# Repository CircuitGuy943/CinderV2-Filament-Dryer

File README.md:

# Cinder Filament Dryer - A fully featured 90W filament dryer for all your drying needs!

The cinder filament dryer is a self managed ecosystem comprising of 2 45W heaters powered from a 90W+ power supply to provide the most heating power possible. In addition to that, there is also space for 3 possible fans with silica gel pouch to aid in the airflow and dryer performance. Equiped with an SHT40 module, you will always be 110% aware of exactly how long your filament will take to dry and at what temperature and with a 90W heater, I can guarantee that won't be long ;). Also comes in a cool, tilted design with a fancy flame aesthetic on the side, it also utilizes a smart locking system that adapts the arm of the spool holder to the width of the spool hole, this way, you can ensure the spool is free to spin properly and doesn't scratch the heating element. And if that isn't enough filament flow for you, there is also a dedicated servo driving system and filament extrusion rate feedback integration that automatically pushes out the strand of filament so that the printer, or you, don't have to worry about printing while drying. Comes with a 128x64 OLED, 3 buttons and an encoder for all your "control panel" needs because, we all love fancy control panels don't we? The frame itself is designed to be easy to print (albeit quite large) and assemble. And not to mention with the amazing aesthetic comes a super cool futuristic, pod like door system that lifts upwars on a big pin hinge to allow you to remove the spools or insert more. And obviously, we don't want tipping dryers so, on another pin hinge, we have a leg that can be bent backwards flush to the device when the dryer is hung on the wall or extended so that it literally doesn't fall over.

Some CAD images:

## Features:
- It drys filament (duh)
- 90W heating power
- OLED display control panel with 3 buttons, encoder and a cool acrylic view panel
- Leg (pretty simple) to hold it from falling backwards
- Fully integrated PCB that drives the 90W heaters, stepper motor driver, OLED, buttons and connectors for all the other sensors.
- Filament pushing system with extruding feedback to maintain proper filament pushing flow
- Easy to assemble
- Airflow powered by 3 5020 fans (LOTS of airflow)
- Spaces for silica gel pouches
- Fancy, cool looking tilted design with flame aesthetics
- Automatic locking system for holding the spool with an arm extendible in diameter <sup>TM</sup>
- PWM control of fans and heater

## PCB
And this is my main PCB. A bit budget restrained otherwise so I had to use some premade sensor modules, the actual flex heater PCB is pretty simple so I won't bother putting it here (but it's in the files):

And the Schematic:

And here are some 3D views as well:

## Firmware Overview
At the current moment there is some, untested firmware in there that's supposed to have the dryer functioning but, I don't actually have it yet so I can't test, in future I will program it properly.

## BOM:

- The actual print (alot, probably like 1-2kg+)
- The main PCB (check KiCad files for all the components and external modules)
- 3 5020 fans
- A stepper motor
- Some lasercut acrylic
- MX keycaps (3)
- Some M2 heated inserts and bolts to hold the whole thing togethor

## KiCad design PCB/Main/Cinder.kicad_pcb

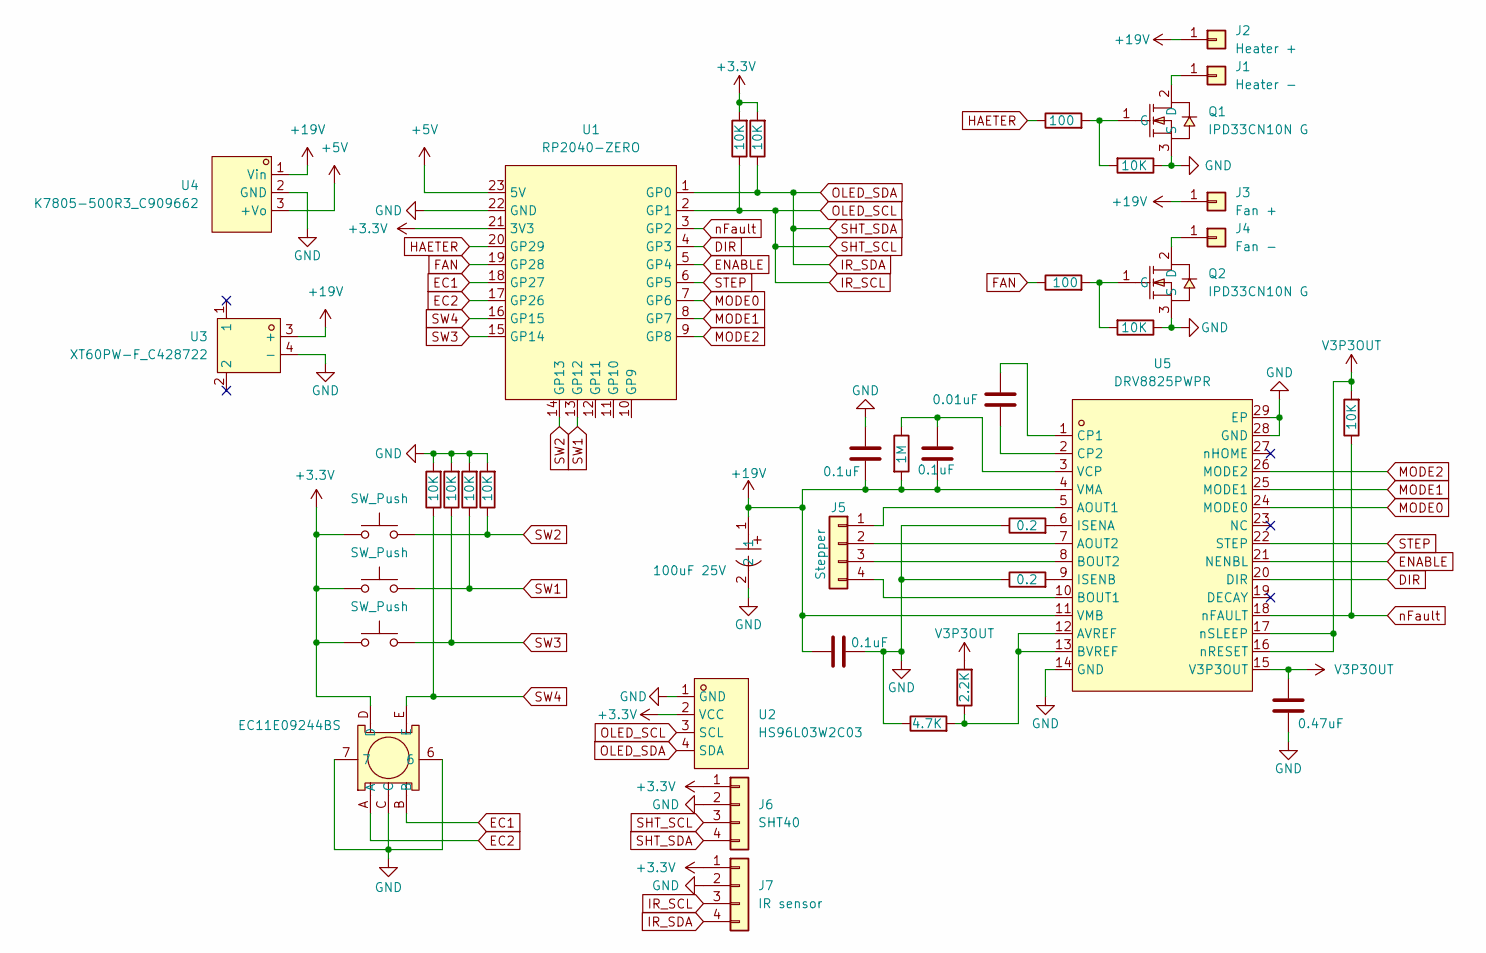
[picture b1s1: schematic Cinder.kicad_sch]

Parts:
C1: 0.01uF; C_1206_3216Metric_Pad1.33x1.80mm_HandSolder
C2, C3, C4: 0.1uF; C_1206_3216Metric_Pad1.33x1.80mm_HandSolder
C5: 0.47uF; C_1206_3216Metric_Pad1.33x1.80mm_HandSolder
J1: Heater -; PinHeader_1x01_P2.54mm_Vertical
J2: Heater +; PinHeader_1x01_P2.54mm_Vertical
J3: Fan +; PinHeader_1x01_P2.54mm_Vertical
J4: Fan -; PinHeader_1x01_P2.54mm_Vertical
J5: Stepper; PinHeader_1x04_P2.54mm_Vertical
J6: SHT40; PinHeader_1x04_P2.54mm_Vertical
J7: IR sensor; PinHeader_1x04_P2.54mm_Vertical
Q1, Q2: IPD33CN10N G; TO-252-2_L6.6-W6.1-P4.57-LS9.9-TL-CW; LCSC Part C536760
R1, R2: 100; R_1206_3216Metric_Pad1.30x1.75mm_HandSolder
R3, R4, R5, R6, R7, R8, R15, R16, R17: 10K; R_1206_3216Metric_Pad1.30x1.75mm_HandSolder
R9: 1M; R_1206_3216Metric_Pad1.30x1.75mm_HandSolder
R10, R11: 0.2; R_1206_3216Metric_Pad1.30x1.75mm_HandSolder
R12: 2.2K; R_1206_3216Metric_Pad1.30x1.75mm_HandSolder
R13: 4.7K; R_1206_3216Metric_Pad1.30x1.75mm_HandSolder
SW1, SW2, SW3: SW_Push; SW_Cherry_MX_1.00u_PCB
SW9: EC11E09244BS; SW-TH_EC11XXXXXXXX; LCSC Part C470742
U1: RP2040-ZERO; COMM-SMD_RP2040-ZERO; LCSC Part C5350143
U2: HS96L03W2C03; OLED-TH_L27.8-W27.2-P2.54_C9900033791; LCSC Part C5248080
U3: XT60PW-F_C428722; TH_2P-XT60PW-F; LCSC Part C428722
U4: K7805-500R3_C909662; PWRM-TH_K78XX-500R3; LCSC Part C909662
U5: DRV8825PWPR; HTSSOP-28_L9.7-W4.4-P0.65-LS6.4-BL-EP5.5; LCSC Part C81582
U6: 100uF 25V; CAP-SMD_BD6.3-L6.6-W6.6-LS7.2-FD-1; LCSC Part C970685

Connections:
+3.3V: J6.1, J7.1, R16.2, R17.2, SW1.1, SW2.1, SW3.1, SW9.D, U1.21 (3V3), U2.2 (VCC)
+5V: U1.23 (5V), U4.3 (+Vo)
+19V: C2.2, C3.1, C4.1, J2.1, J3.1, R9.2, U3.3 (+), U4.1 (Vin), U5.4 (VMA), U5.11 (VMB), U6.1
DIR: U1.4 (GP3), U5.20 (DIR)
EC1: SW9.B, U1.18 (GP27)
EC2: SW9.A, U1.17 (GP26)
ENABLE: U1.5 (GP4), U5.21 (NENBL)
FAN: R2.1, U1.19 (GP28)
GND: C3.2, C4.2, C5.2, J6.2, J7.2, Q1.3 (S), Q2.3 (S), R3.1, R4.1, R5.2, R6.2, R7.2, R8.2, R10.1, R11.1, R13.1, SW9.6, SW9.7, SW9.C, U1.22 (GND), U2.1 (GND), U3.4 (-), U4.2 (GND), U5.14 (GND), U5.28 (GND), U5.29 (EP), U6.2
HAETER: R1.1, U1.20 (GP29)
IR_SCL: J6.3, J7.3, R16.1, U1.2 (GP1), U2.3 (SCL)
IR_SDA: J6.4, J7.4, R17.1, U1.1 (GP0), U2.4 (SDA)
MODE0: U1.7 (GP6), U5.24 (MODE0)
MODE1: U1.8 (GP7), U5.25 (MODE1)
MODE2: U1.9 (GP8), U5.26 (MODE2)
unnamed: J1.1, Q1.2 (D)
unnamed: J4.1, Q2.2 (D)
unnamed: J5.1, U5.5 (AOUT1)
unnamed: J5.2, U5.7 (AOUT2)
unnamed: J5.3, U5.8 (BOUT2)
unnamed: J5.4, U5.10 (BOUT1)
unnamed: Q1.1 (G), R1.2, R4.2
unnamed: Q2.1 (G), R2.2, R3.2
unnamed: R12.1, R13.2, U5.12 (AVREF), U5.13 (BVREF)
unnamed: C1.1, U5.1 (CP1)
unnamed: C1.2, U5.2 (CP2)
unnamed: R10.2, U5.6 (ISENA)
unnamed: R11.2, U5.9 (ISENB)
unnamed: C2.1, R9.1, U5.3 (VCP)
STEP: U1.6 (GP5), U5.22 (STEP)
SW1: R6.1, SW1.2, U1.13 (GP12)
SW2: R5.1, SW2.2, U1.14 (GP13)
SW3: R7.1, SW3.2, U1.15 (GP14)
SW4: R8.1, SW9.E, U1.16 (GP15)
V3P3OUT: C5.1, R12.2, R15.2, U5.15 (V3P3OUT), U5.16 (nRESET), U5.17 (nSLEEP)
nFault: R15.1, U1.3 (GP2), U5.18 (nFAULT)

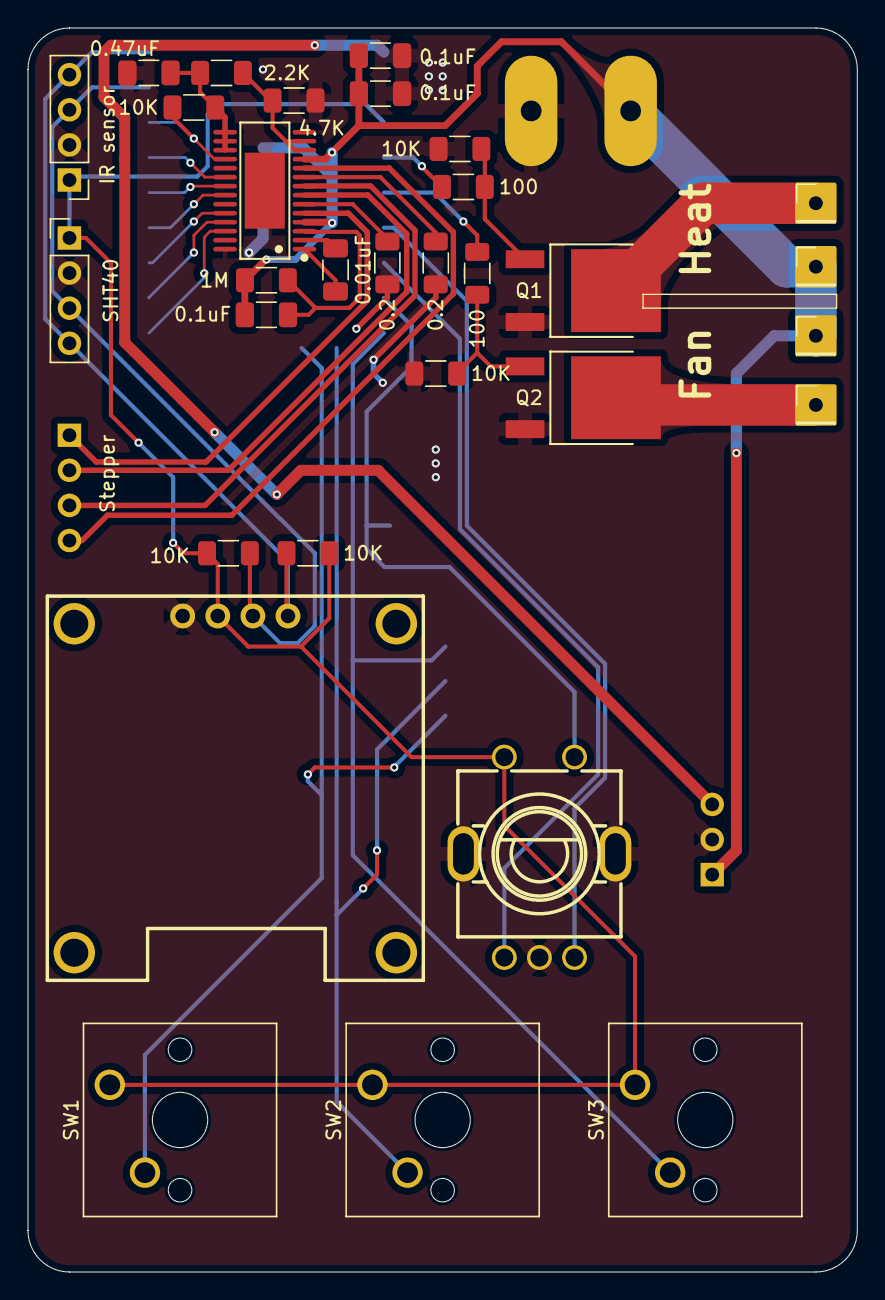
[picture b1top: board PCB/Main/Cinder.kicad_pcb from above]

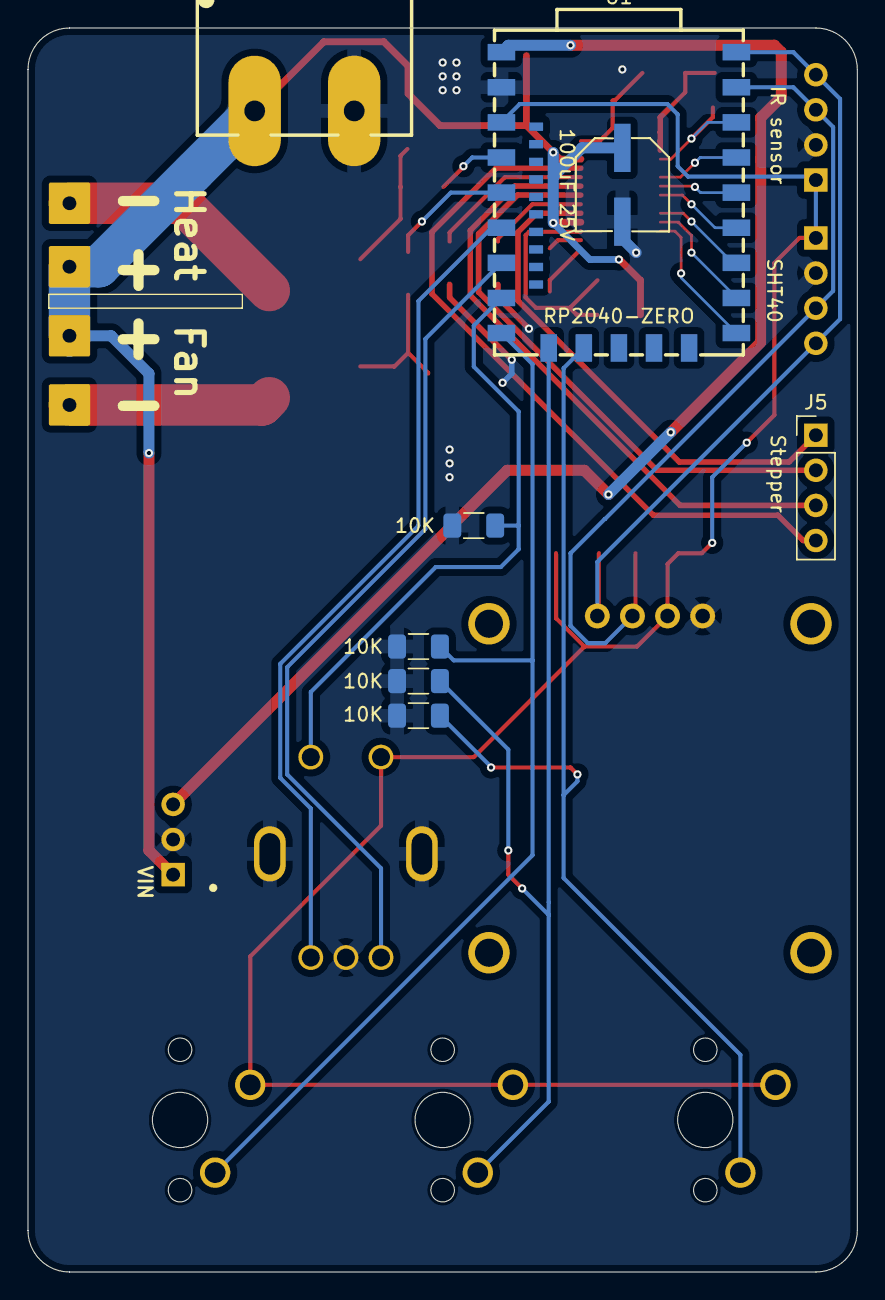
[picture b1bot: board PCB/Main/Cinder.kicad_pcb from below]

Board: 2 copper layers, 60.0 x 90.0 mm, 40 parts (9 on the bottom side), 36 nets.

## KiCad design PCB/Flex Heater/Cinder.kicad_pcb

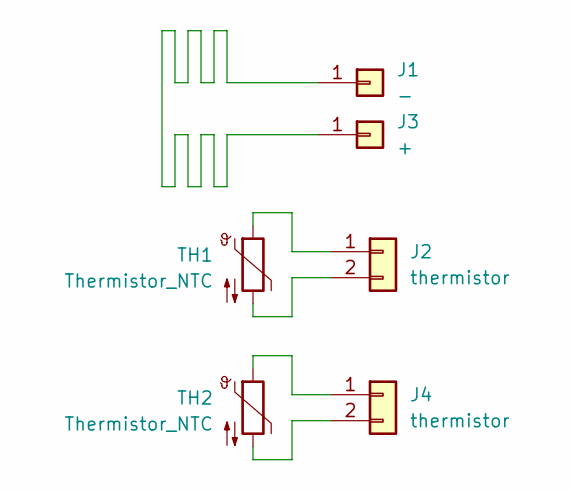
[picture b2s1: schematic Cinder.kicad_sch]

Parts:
J1: -; PinHeader_1x01_P1.00mm_Vertical
J2, J4: thermistor; PinHeader_1x02_P1.00mm_Vertical
J3: +; PinHeader_1x01_P1.00mm_Vertical
TH1, TH2: Thermistor_NTC; R_0603_1608Metric

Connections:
unnamed: J1.1, J3.1
unnamed: J2.1, TH1.1
unnamed: J2.2, TH1.2
unnamed: J4.1, TH2.1
unnamed: J4.2, TH2.2

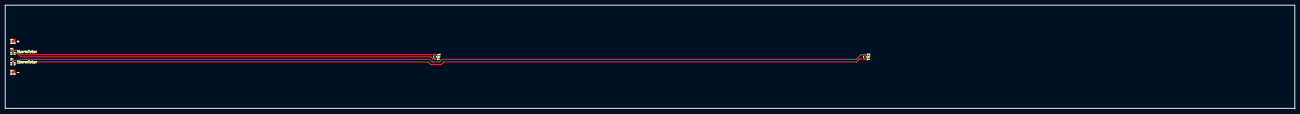
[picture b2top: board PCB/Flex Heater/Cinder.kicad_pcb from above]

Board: 2 copper layers, 500.0 x 40.0 mm, 6 parts (0 on the bottom side), 5 nets.

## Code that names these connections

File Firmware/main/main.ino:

#include <Encoder.h>
#include <Bounce2.h>
#define DUMP_REGS
#include <Wire.h>
#include <APDS9930.h>

#include <Arduino.h>
#include <U8g2lib.h>

#ifdef U8X8_HAVE_HW_SPI
#include <SPI.h>
#endif
#ifdef U8X8_HAVE_HW_I2C
#include <Wire.h>
#endif

// Define pins
const int heater = 29;  // Timer0
const int fan = 28;  // Timer0 or Timer1 depending on board


Encoder myEnc(26, 27);

APDS9930 apds = APDS9930();
uint16_t proximity_data = 0;

// ================== BUTTONS ==================
Bounce btn1;
Bounce btn2;
Bounce btn3;
Bounce btn4;

constexpr uint8_t BTN_1_PIN = 12;
constexpr uint8_t BTN_2_PIN = 13;
constexpr uint8_t BTN_3_PIN = 14;
constexpr uint8_t BTN_4_PIN = 15;
// ================================================

AccelStepper stepper(AccelStepper::DRIVER, 5, 2);
const int enable_pin = 4;
const int mode0 = 6;
const int mode1 = 7;
const int mode2 = 8;



void setupButtons() {
  pinMode(BTN_1_PIN, INPUT);
  pinMode(BTN_2_PIN, INPUT);
  pinMode(BTN_3_PIN, INPUT);
  pinMode(BTN_4_PIN, INPUT);

  btn1.attach(BTN_1_PIN);
  btn2.attach(BTN_2_PIN);
  btn3.attach(BTN_3_PIN);
  btn4.attach(BTN_4_PIN);

  btn1.interval(10);
  btn2.interval(10);
  btn3.interval(10);
  btn4.interval(10);
}
void filamentSensorSetup() {
  Serial.println(F("---------------------------"));
  Serial.println(F("APDS-9930 - ProximitySensor"));
  Serial.println(F("---------------------------"));

  if ( apds.init() ) {
    Serial.println(F("APDS-9930 initialization complete"));
  } else {
    Serial.println(F("Something went wrong during APDS-9930 init!"));
  }

  // // Adjust the Proximity sensor gain
  // if ( !apds.setProximityGain(PGAIN_2X) ) {
  //   Serial.println(F("Something went wrong trying to set PGAIN"));
  // }

  if ( apds.enableProximitySensor(false) ) {
    Serial.println(F("Proximity sensor is now running"));
  } else {
    Serial.println(F("Something went wrong during sensor init!"));
  }
}
#ifdef DUMP_REGS
  /* Register dump */
  uint8_t reg;
  uint8_t val;

  for(reg = 0x00; reg <= 0x19; reg++) {
    if( (reg != 0x10) && \
        (reg != 0x11) )
    {
      apds.wireReadDataByte(reg, val);
      Serial.print(reg, HEX);
      Serial.print(": 0x");
      Serial.println(val, HEX);
    }
  }
  apds.wireReadDataByte(0x1E, val);
  Serial.print(0x1E, HEX);
  Serial.print(": 0x");
  Serial.println(val, HEX);
#endif
}
void oledSetup(): {
  U8G2_SSD1306_128X64_NONAME_F_HW_I2C u8g2(U8G2_R0, /* reset=*/ U8X8_PIN_NONE);
  u8g2.begin();
}
void shtSetup(): {
  while (!Serial)
    delay(10);     // will pause Zero, Leonardo, etc until serial console opens

  Serial.println("Adafruit SHT4x test");
  if (! sht4.begin()) {
    Serial.println("Couldn't find SHT4x");
    while (1) delay(1);
  }
  Serial.println("Found SHT4x sensor");
  Serial.print("Serial number 0x");
  Serial.println(sht4.readSerial(), HEX);

  // You can have 3 different precisions, higher precision takes longer
  sht4.setPrecision(SHT4X_HIGH_PRECISION);
  switch (sht4.getPrecision()) {
     case SHT4X_HIGH_PRECISION: 
       Serial.println("High precision");
       break;
     case SHT4X_MED_PRECISION: 
       Serial.println("Med precision");
       break;
     case SHT4X_LOW_PRECISION: 
       Serial.println("Low precision");
       break;
  }

  // You can have 6 different heater settings
  // higher heat and longer times uses more power
  // and reads will take longer too!
  sht4.setHeater(SHT4X_NO_HEATER);
  switch (sht4.getHeater()) {
     case SHT4X_NO_HEATER: 
       Serial.println("No heater");
       break;
     case SHT4X_HIGH_HEATER_1S: 
       Serial.println("High heat for 1 second");
       break;
     case SHT4X_HIGH_HEATER_100MS: 
       Serial.println("High heat for 0.1 second");
       break;
     case SHT4X_MED_HEATER_1S: 
       Serial.println("Medium heat for 1 second");
       break;
     case SHT4X_MED_HEATER_100MS: 
       Serial.println("Medium heat for 0.1 second");
       break;
     case SHT4X_LOW_HEATER_1S: 
       Serial.println("Low heat for 1 second");
       break;
     case SHT4X_LOW_HEATER_100MS: 
       Serial.println("Low heat for 0.1 second");
       break;
  }
  
}


void setup() {
  Wire.setSDA(0);
  Wire.setSCL(1);

  oledSetup();

  filamentSensorSetup();

  shtSetup();

  setupButtons();

  pinMode(heater, OUTPUT);
  pinMode(fan, OUTPUT);

  pinMode(enable_pin, OUTPUT);

  stepper.setMaxSpeed(1000); // steps/sec
  stepper.setAcceleration(500); // steps/sec^2

  Serial.begin(9600);
  Serial.println("Basic Functionality Firmware");
}


void updateButtons() {
  btn1.update();
  btn2.update();
  btn3.update();
  btn4.update();

  if (btn1.fell()) onButton1Press();
  if (btn2.fell()) onButton2Press();
  if (btn3.fell()) onButton3Press();
  if (btn4.fell()) onButton4Press();
}
void updateEncoder() {
  long newPosition = myEnc.read();
  if (newPosition != oldPosition) {
    oldPosition = newPosition;
    Serial.println("Encoder Position: " + str(newPosition));
  }
}
void updateOLED(): {
  u8g2.clearBuffer();					// clear the internal memory
  u8g2.setFont(u8g2_font_ncenB08_tr);	// choose a suitable font
  u8g2.drawStr(0,10,"Hello World!");	// write something to the internal memory
  u8g2.sendBuffer();					// transfer internal memory to the display
}
void readProximitySensor(): {
  if ( !apds.readProximity(proximity_data) ) {
  Serial.println("Error reading proximity value");
  }
  else {
  Serial.print("Proximity: ");
  Serial.println(proximity_data);
  }
}
void readSHT40(): {
  sensors_event_t humidity, temp;
  
  uint32_t timestamp = millis();
  sht4.getEvent(&humidity, &temp);// populate temp and humidity objects with fresh data
  timestamp = millis() - timestamp;

  Serial.print("Temperature: "); Serial.print(temp.temperature); Serial.println(" degrees C");
  Serial.print("Humidity: "); Serial.print(humidity.relative_humidity); Serial.println("% rH");

  Serial.print("Read duration (ms): ");
  Serial.println(timestamp);
}


long oldPosition  = -999;

void loop() {
  updateEncoder():
  updateButtons();
  updateOLED();
  readProximitySensor();
  readSHT40(); 
  analogWrite(heater, 64); // 25% duty cycle
  analogWrite(fan, 192); // 75% duty cycle

  digitalWrite(enable_pin, LOW);
  digitalWrite(mode0, HIGH);
  digitalWrite(mode1, LOW);
  digitalWrite(mode2, LOW);
  stepper.moveTo(100); // move 2000 steps
  stepper.run();
  delay(1000);
}





void onButton1Press() {
  Serial.println("Button 1 pressed");
}

void onButton2Press() {
  Serial.println("Button 2 pressed");
}

void onButton3Press() {
  Serial.println("Button 3 pressed");
}

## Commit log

2026-01-07 PyCharm stuff
2026-01-14 Update - Done main PCB
2026-01-14 Changed images
2026-02-02 Update with CAD files and pictures
2026-02-02 Add video
2026-02-02 Video
2026-02-02 Revise README for Cinder Filament Dryer details
    Updated the README to provide a detailed description of the Cinder Filament Dryer, including features, PCB information, firmware overview, and BOM.
2026-02-02 Update README with CAD and PCB images
    Added CAD images and updated PCB images in README.
2026-02-02 Enhance README with dryer details and images
    Added detailed description of the cinder filament dryer and included images.
